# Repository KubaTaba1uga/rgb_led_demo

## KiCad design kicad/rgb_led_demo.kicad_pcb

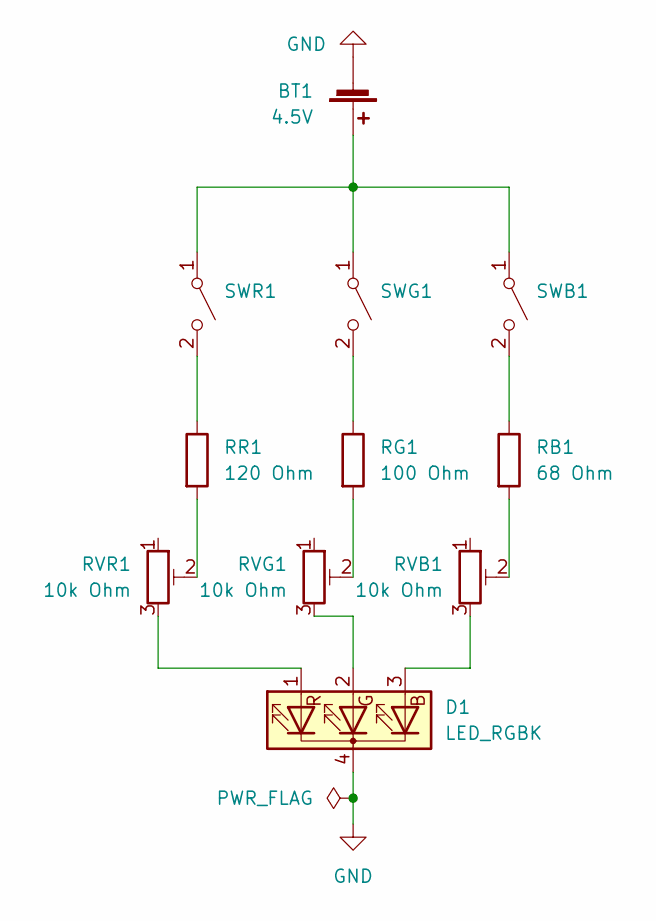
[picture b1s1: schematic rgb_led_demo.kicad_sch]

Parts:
BT1: 4.5V; BatteryHolder_Keystone_2479_3xAAA
D1: LED_RGBK; LED_D5.0mm-4_RGB
RB1: 68 Ohm; R_Axial_DIN0207_L6.3mm_D2.5mm_P7.62mm_Horizontal
RG1: 100 Ohm; R_Axial_DIN0207_L6.3mm_D2.5mm_P7.62mm_Horizontal
RR1: 120 Ohm; R_Axial_DIN0207_L6.3mm_D2.5mm_P7.62mm_Horizontal
RVB1: 10k Ohm; Potentiometer_Alps_RK163_Single_Horizontal
RVG1: 10k Ohm; Potentiometer_Alps_RK163_Single_Horizontal
RVR1: 10k Ohm; Potentiometer_Alps_RK163_Single_Horizontal
SWB1: SW_SPST; SW_DIP_SPSTx01_Slide_9.78x4.72mm_W7.62mm_P2.54mm
SWG1: SW_SPST; SW_DIP_SPSTx01_Slide_9.78x4.72mm_W7.62mm_P2.54mm
SWR1: SW_SPST; SW_DIP_SPSTx01_Slide_9.78x4.72mm_W7.62mm_P2.54mm

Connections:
GND: BT1.2 (-), D1.4 (K)
unnamed: BT1.1 (+), SWB1.1 (A), SWG1.1 (A), SWR1.1 (A)
unnamed: D1.1 (RA), RVR1.3
unnamed: D1.2 (GA), RVG1.3
unnamed: D1.3 (BA), RVB1.3
unnamed: RB1.1, SWB1.2 (B)
unnamed: RB1.2, RVB1.2
unnamed: RG1.1, SWG1.2 (B)
unnamed: RG1.2, RVG1.2
unnamed: RR1.1, SWR1.2 (B)
unnamed: RR1.2, RVR1.2

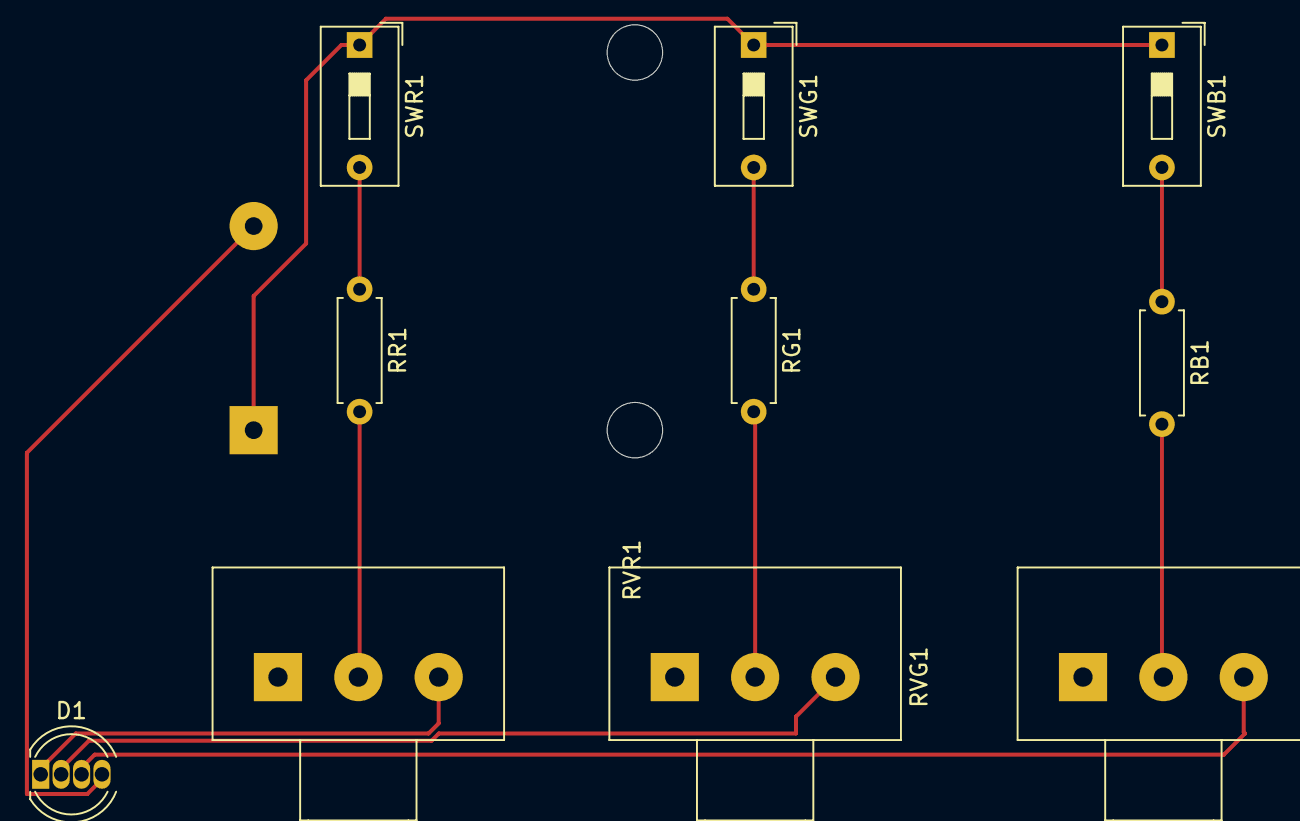
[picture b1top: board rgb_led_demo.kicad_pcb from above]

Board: 2 copper layers, 11 parts (1 on the bottom side), 11 nets.

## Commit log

2024-09-12 init kicad project
2024-09-12 create draft of electric schematics
2024-09-17 finish up creating schematics
2024-09-17 add pcb board design
